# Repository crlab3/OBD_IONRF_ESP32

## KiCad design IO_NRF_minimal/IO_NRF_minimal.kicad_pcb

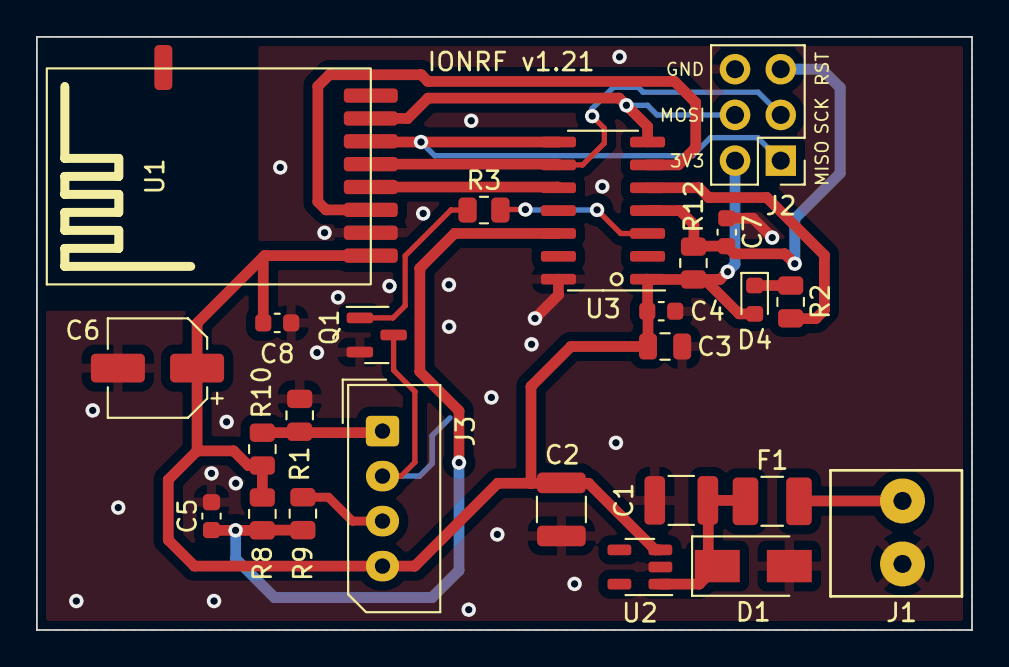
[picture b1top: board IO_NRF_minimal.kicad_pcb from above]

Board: 2 copper layers, 52.0 x 33.0 mm, 26 parts (1 on the bottom side), 18 nets.

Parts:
C1, C2: 10uF; C_1210_3225Metric
C3: 4.7uF; C_0805_2012Metric
C4, C5, C7, C8: 100nF; C_0603_1608Metric
C6: 100uF; CP_Elec_5x5.3
D1: DO-214AC; D_SMA
D4: LED; LED_0603_1608Metric
F1: 100mA Polyfuse; Fuse_1210_3225Metric_Pad1.42x2.65mm_HandSolder
J1: 12V_IN; SORKAPOCS-3.5mm-2
J2: Programmer_Pins_SPI; PinHeader_2x03_P2.54mm_Vertical
J3: XKC-Y2S-IN; Molex_SPOX_5267-04A_1x04_P2.50mm_Vertical
JP1: SolderJumper_2_Open; SolderJumper-2_P1.3mm_Open_RoundedPad1.0x1.5mm
Q1: BC847B; SOT-23
R1, R2, R3, R8, R9, R10, R12: 1k; R_0805_2012Metric
U1: NRF24L01_SMD
U2: AP7370-33WW-7; SOT-23-5
U3: ATtiny84-20SS; SOIC-14_3.9x8.7mm_P1.27mm

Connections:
/3V3: C2.1, C3.1, C4.1, C6.1, C8.2, D4.2 (A), J2.2, J3.4, R8.1, R10.1, R12.1, U1.1 (3V3), U2.3 (VOUT(3.3V)), U3.1 (VCC)
/ACC_12V_IN: F1.2, J1.2
/ACC_12V_PROT: C1.1, D1.1 (K), F1.1, U2.1 (VIN)
/MCU_MISO: J2.1, U1.6 (MOSI), U3.8 (PA5)
/MCU_MOSI: J2.4, U1.7 (MISO), U3.7 (PA6)
/MCU_RESET: C7.2, J2.5, R12.2, U3.4 (~RESET/PB3)
/MCU_SCK: J2.3, U1.5 (SCK), U3.9 (PA4)
/NRF_CE: U1.3 (CE), U3.6 (PA7)
/NRF_CS: U1.4 (CSN), U3.10 (PA3)
/XKC-Y2S-IN: C5.2, R8.2, R9.2, U3.12 (PA1)
/XKC_ACTIVATE: R3.2, U3.3 (XTAL2/PB1)
GND: C1.2, C2.2, C3.2, C4.2, C5.1, C6.2, C7.1, C8.1, D1.2 (A), J1.1, J2.6, JP1.1 (A), Q1.2 (E), R1.1, U1.2 (GND), U2.2 (GND), U3.14 (GND)
unnamed: D4.1 (K), R2.1
unnamed: J3.1, R1.2, R10.2
unnamed: J3.2, JP1.2 (B), Q1.3 (C)
unnamed: J3.3, R9.1
unnamed: Q1.1 (B), R3.1
unnamed: R2.2, U3.5 (PB2)

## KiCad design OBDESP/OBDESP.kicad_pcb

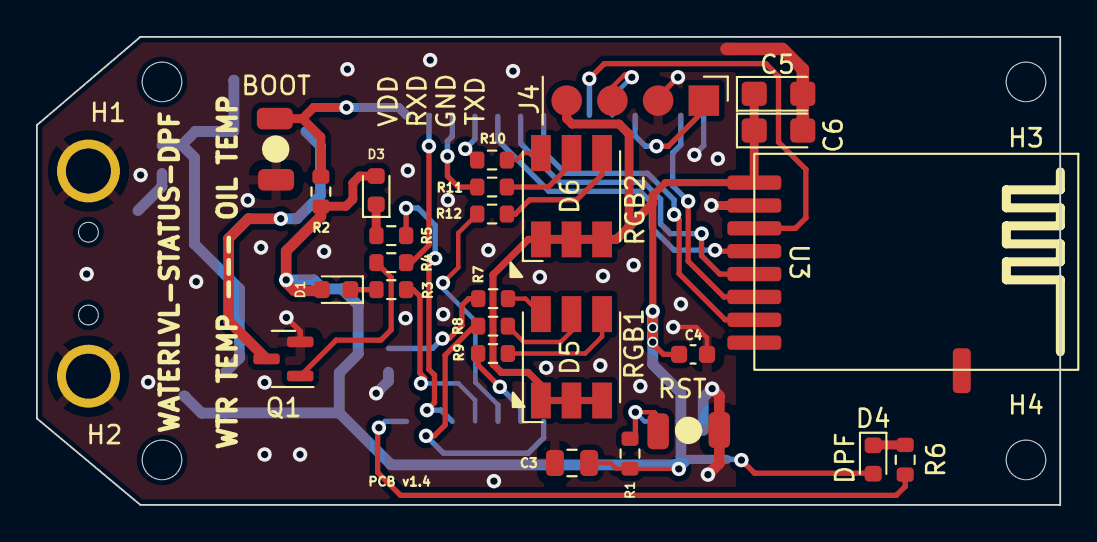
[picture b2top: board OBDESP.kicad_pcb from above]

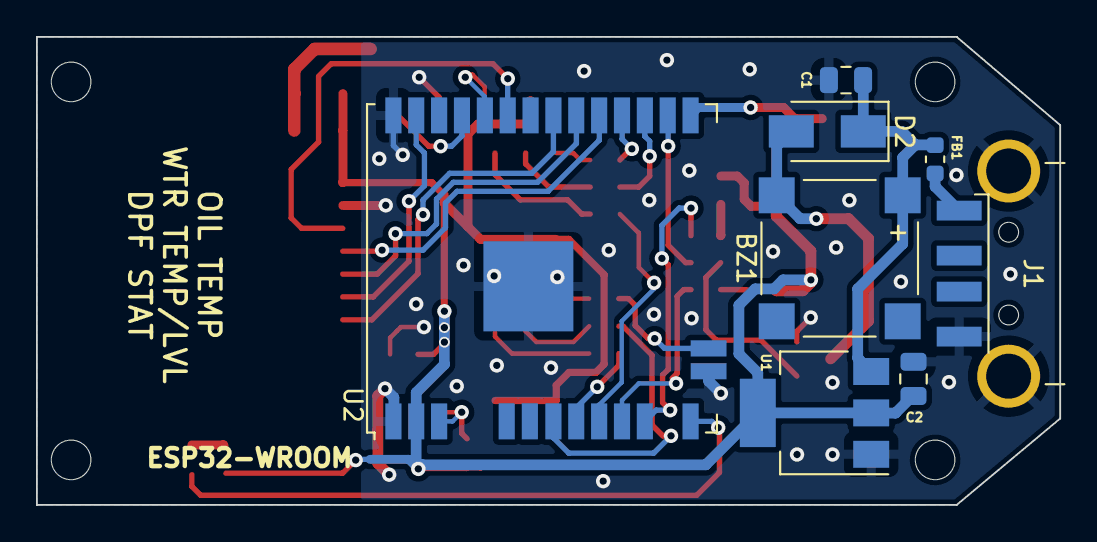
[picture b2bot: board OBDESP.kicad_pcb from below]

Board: 2 copper layers, 56.8 x 26.0 mm, 38 parts (8 on the bottom side), 34 nets.

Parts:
BZ1: Buzzer; PUIAudio_SMT_0825_S_4_R
C1, C2, C3: 10uF; C_0805_2012Metric
C4: 100nF; C_0603_1608Metric
C5, C6: 22uF; CP_EIA-3216-18_Kemet-A
D1: GREEN_LED; LED_0603_1608Metric
D2: D; D_SMA
D3: YELLOW_LED; LED_0603_1608Metric
D4: WHITE_LED; LED_0603_1608Metric
D5, D6: LED_RGB; LED_RGB_5050-6
FB1: FerriteBead_Small; L_0603_1608Metric
H1, H2, H3, H4: MountingHole; MountingHole_2.2mm_M2_DIN965
J1: USB_A; USB_A_CNCTech_1001-011-01101_Horizontal
J2: RST; B3U-1000P_Button
J3: BOOT; B3U-1000P_Button
J4: UART; PinHeader_1x04_P2.54mm_Vertical
Q1: BC848CLT1G; SOT-23
R1, R2: 10k; R_0603_1608Metric
R3, R4, R5: 220; R_0603_1608Metric
R6, R7, R8, R9, R10, R11, R12: 100; R_0603_1608Metric
U1: NCP1117-3.3_DPAK; SOT-223-3_TabPin2
U2: ESP32-WROOM-32; ESP32-WROOM-32U
U3: NRF24L01_SMD

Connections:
/3.3V: C2.2, C3.1, C4.1, C5.1, C6.1, D1.2 (A), D3.2 (A), D4.2 (A), D5.1 (RA), D5.2 (GA), D5.3 (BA), D6.1 (RA), D6.2 (GA), D6.3 (BA), J4.4, R1.1, R2.1, U1.2 (VO), U2.2 (VDD), U3.1 (3V3)
/COOLANTSTATUS_LED: R5.1, U2.12 (IO27)
/DPF_LED: R6.1, U2.14 (IO12)
/NRF_CE: U2.33 (IO21), U3.3 (CE)
/NRF_CSN: U2.29 (IO5), U3.4 (CSN)
/NRF_MISO: U2.31 (IO19), U3.7 (MISO)
/NRF_MOSI: U2.37 (IO23), U3.6 (MOSI)
/NRF_SCK: U2.30 (IO18), U3.5 (SCK)
/RGB1_B: R9.1, U2.9 (IO33)
/RGB1_G: R7.1, U2.16 (IO13)
/RGB1_R: R8.1, U2.8 (IO32)
/RGB2_B: R12.1, U2.10 (IO25)
/RGB2_G: R10.1, U2.28 (IO17)
/RGB2_R: R11.1, U2.27 (IO16)
/STATUS1_LED: R3.1, U2.11 (IO26)
/VIN: BZ1.1 (-), C1.2, D2.1 (K), FB1.2, U1.3 (VI)
/WARNING_BUZZER: R4.1, U2.26 (IO4)
GND: C1.1, C2.1, C3.2, C4.2, C5.2, C6.2, J1.4 (GND), J1.5 (Shield), J2.1, J3.1, J4.2, Q1.2 (E), U1.1 (GND), U2.1 (GND), U2.15 (GND), U2.38 (GND), U2.39 (GND), U3.2 (GND)
unnamed: BZ1.2 (+), D2.2 (A), Q1.3 (C)
unnamed: D1.1 (K), R3.2
unnamed: D5.4 (BK), R9.2
unnamed: D5.5 (GK), R8.2
unnamed: D5.6 (RK), R7.2
unnamed: D6.4 (BK), R12.2
unnamed: D6.5 (GK), R11.2
unnamed: D6.6 (RK), R10.2
unnamed: FB1.1, J1.1 (VBUS)
unnamed: J2.2, R1.2, U2.3 (EN)
unnamed: J3.2, R2.2, U2.25 (IO0)
unnamed: J4.1, U2.35 (TXD0/IO1)
unnamed: J4.3, U2.34 (RXD0/IO3)
unnamed: Q1.1 (B), R4.2
unnamed: D3.1 (K), R5.2
unnamed: D4.1 (K), R6.2

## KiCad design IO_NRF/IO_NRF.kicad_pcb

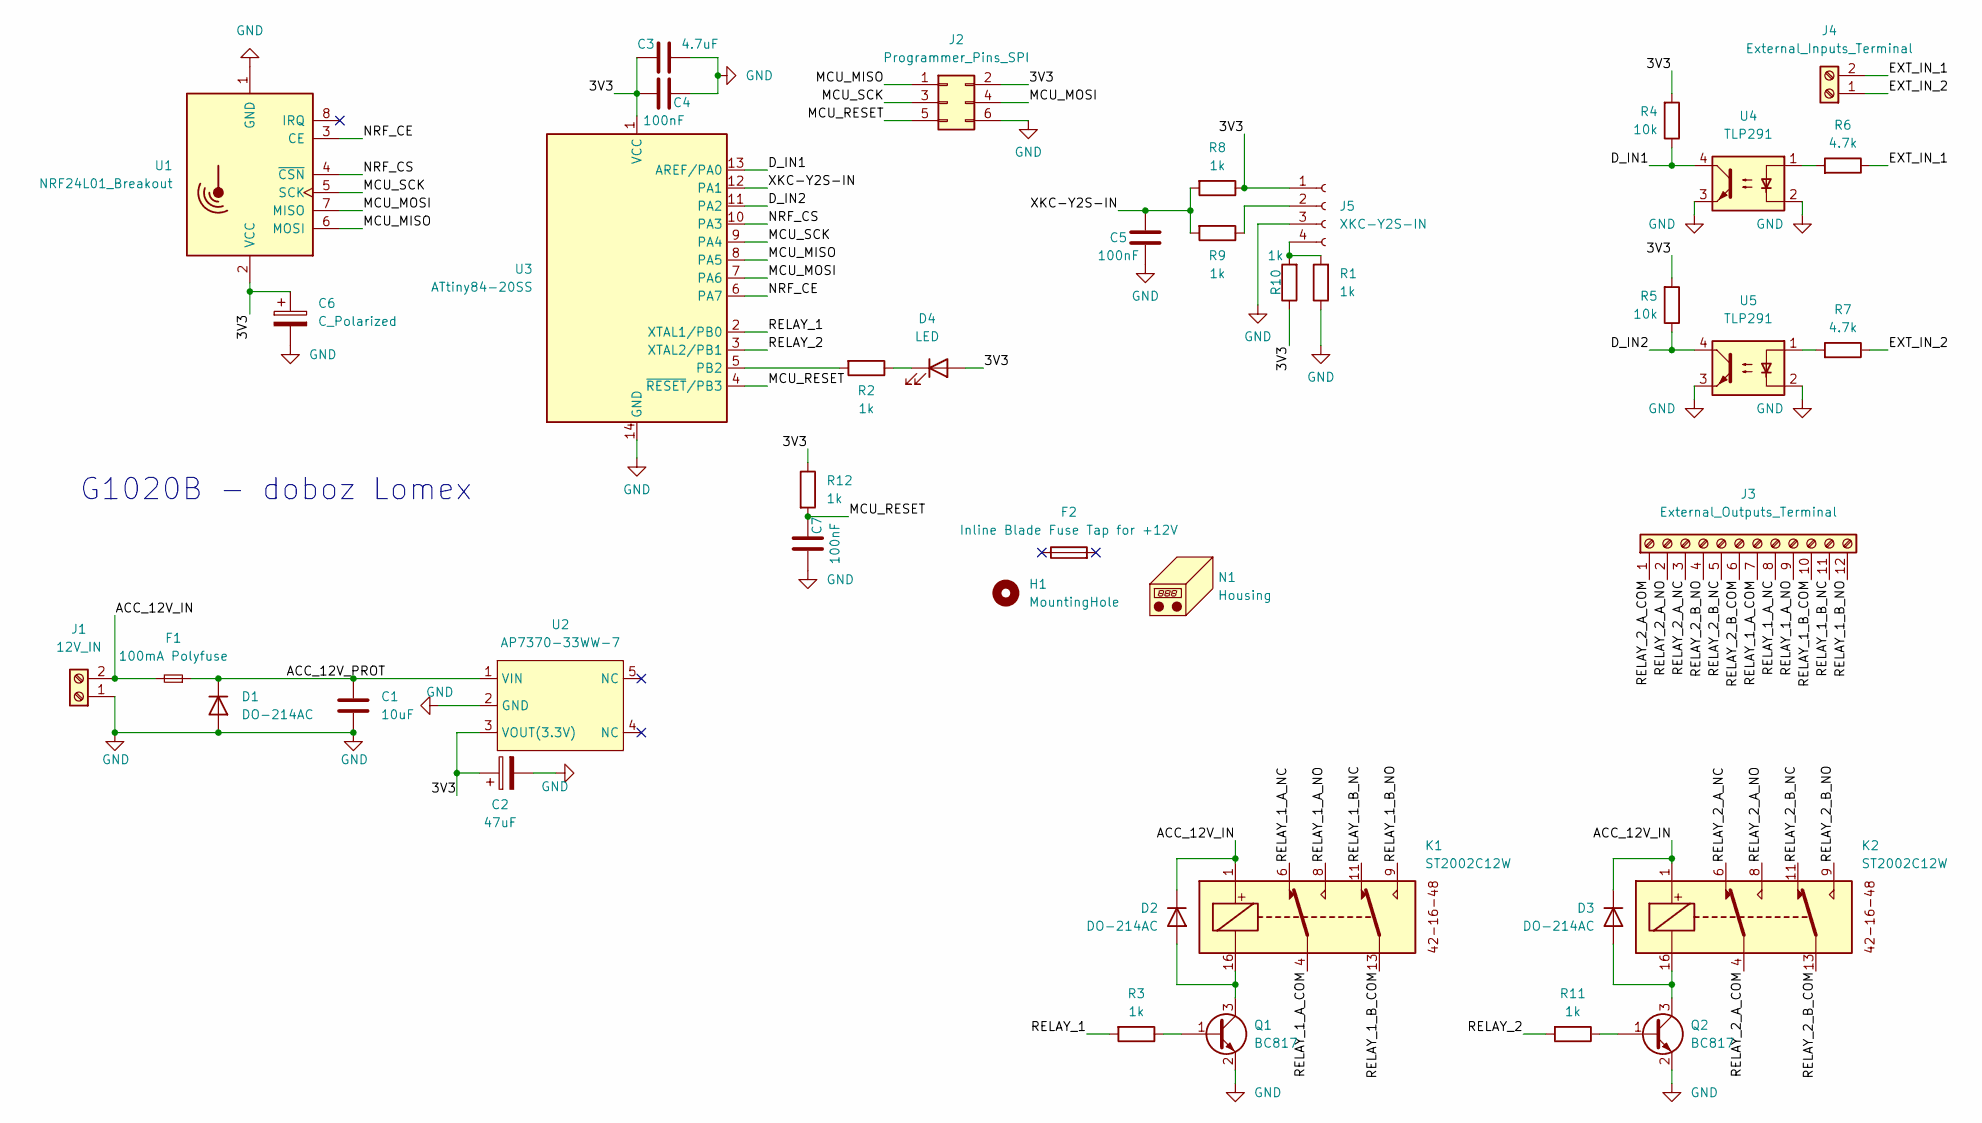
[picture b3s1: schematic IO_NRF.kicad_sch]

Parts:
C1: 10uF; C_1210_3225Metric
C2: 47uF; CP_Elec_6.3x5.4
C3: 4.7uF; C_0805_2012Metric
C4, C5, C7: 100nF; C_0603_1608Metric
C6: C_Polarized; CP_Elec_5x5.3
D1, D2, D3: DO-214AC; D_SMA
D4: LED; LED_0603_1608Metric
F1: 100mA Polyfuse; Fuse_1210_3225Metric_Pad1.42x2.65mm_HandSolder
F2: Inline Blade Fuse Tap for +12V; Farnell 3227155
H1: MountingHole; MountingHole_3.2mm_M3
J1: 12V_IN; SORKAPOCS-3.5mm-2
J2: Programmer_Pins_SPI; PinHeader_2x03_P2.54mm_Vertical
J3: External_Outputs_Terminal; SORKAPOCS-3.5mm-12
J4: External_Inputs_Terminal; SORKAPOCS-3.5mm-2
J5: XKC-Y2S-IN; PinSocket_1x04_P2.54mm_Vertical
K1, K2: ST2002C12W
N1: Housing
Q1, Q2: BC817; SOT-23
R1, R2, R3, R8, R9, R10, R11, R12: 1k; R_0805_2012Metric
R4, R5: 10k; R_0805_2012Metric
R6, R7: 4.7k; R_0805_2012Metric
U1: NRF24L01_Breakout; PinHeader_2x04_P2.54mm_Vertical
U2: AP7370-33WW-7; SOT-23-5; Mouser 621-AP7370-33WW-7
U3: ATtiny84-20SS; SOIC-14_3.9x8.7mm_P1.27mm; Mouser 556-ATTINY84-20SSUR
U4, U5: TLP291; SOIC-4_4.55x2.6mm_P1.27mm

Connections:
/3V3: C2.1, C3.1, C4.1, C6.1, D4.2 (A), J2.2, J5.1, R4.2, R5.2, R8.1, R10.1, R12.1, U1.2 (VCC), U2.3 (VOUT(3.3V)), U3.1 (VCC)
/ACC_12V_IN: D2.1 (K), D3.1 (K), F1.2, J1.2, K1.1, K2.1
/ACC_12V_PROT: C1.1, D1.1 (K), F1.1, U2.1 (VIN)
/D_IN1: R4.1, U3.13 (AREF/PA0), U4.4
/D_IN2: R5.1, U3.11 (PA2), U5.4
/EXT_IN_1: J4.2, R6.1
/EXT_IN_2: J4.1, R7.1
/MCU_MISO: J2.1, U1.6 (MOSI), U3.8 (PA5)
/MCU_MOSI: J2.4, U1.7 (MISO), U3.7 (PA6)
/MCU_RESET: C7.2, J2.5, R12.2, U3.4 (~RESET/PB3)
/MCU_SCK: J2.3, U1.5 (SCK), U3.9 (PA4)
/NRF_CE: U1.3 (CE), U3.6 (PA7)
/NRF_CS: U1.4 (~CSN), U3.10 (PA3)
/RELAY_1: R3.2, U3.2 (XTAL1/PB0)
/RELAY_1_A_COM: J3.7, K1.4
/RELAY_1_A_NC: J3.8, K1.6
/RELAY_1_A_NO: J3.9, K1.8
/RELAY_1_B_COM: J3.10, K1.13
/RELAY_1_B_NC: J3.11, K1.11
/RELAY_1_B_NO: J3.12, K1.9
/RELAY_2: R11.2, U3.3 (XTAL2/PB1)
/RELAY_2_A_COM: J3.1, K2.4
/RELAY_2_A_NC: J3.3, K2.6
/RELAY_2_A_NO: J3.2, K2.8
/RELAY_2_B_COM: J3.6, K2.13
/RELAY_2_B_NC: J3.5, K2.11
/RELAY_2_B_NO: J3.4, K2.9
/XKC-Y2S-IN: C5.2, R8.2, R9.2, U3.12 (PA1)
GND: C1.2, C2.2, C3.2, C4.2, C5.1, C6.2, C7.1, D1.2 (A), J1.1, J2.6, J5.3, Q1.2 (E), Q2.2 (E), R1.1, U1.1 (GND), U2.2 (GND), U3.14 (GND), U4.2, U4.3, U5.2, U5.3
unnamed: D2.2 (A), K1.16, Q1.3 (C)
unnamed: D3.2 (A), K2.16, Q2.3 (C)
unnamed: D4.1 (K), R2.1
unnamed: J5.2, R9.1
unnamed: J5.4, R1.2, R10.2
unnamed: Q1.1 (B), R3.1
unnamed: Q2.1 (B), R11.1
unnamed: R2.2, U3.5 (PB2)
unnamed: R6.2, U4.1
unnamed: R7.2, U5.1

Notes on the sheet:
G1020B - doboz Lomex

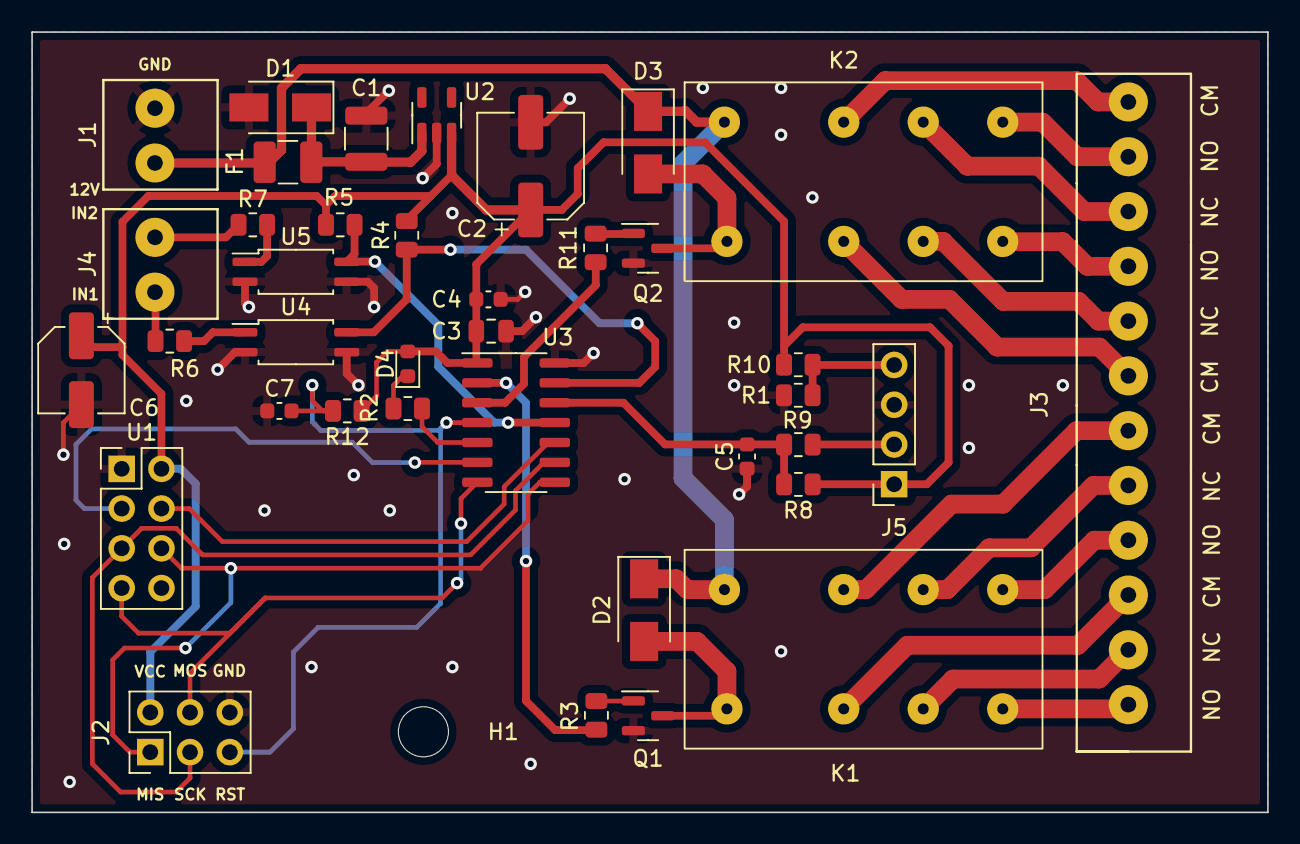
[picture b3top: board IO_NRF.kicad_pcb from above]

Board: 2 copper layers, 79.0 x 49.9 mm, 39 parts (0 on the bottom side), 39 nets.

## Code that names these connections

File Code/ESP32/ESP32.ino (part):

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#define RES_PWM 10
#define LED_MAX 1023

#define NRF_CE 21
#define NRF_CS 5

#define OBD_UPDATE_INTERVAL 100
#define COOLANT_LOW_LIMIT 10
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#define RGB_RIGHT_GREEN 17
#define RGB_RIGHT_BLUE 25 

#define DPF_LED 12
#define STATUS1_LED 26
#define CLNTSTATUS_LED 27

#define BUZZER_PIN 4
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
  //-------------------SETUP LEDs---------------------
  
  uint8_t LEDPins[9]={RGB_RIGHT_RED,RGB_RIGHT_GREEN,RGB_RIGHT_BLUE,RGB_LEFT_RED,RGB_LEFT_GREEN,RGB_LEFT_BLUE,DPF_LED,STATUS1_LED,CLNTSTATUS_LED};
  int i = 0;
  for(i=0; i<9; i++)
  {
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
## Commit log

2022-12-18 Initial commit 1
    New commit for repo
2022-12-31 NRF24L01 Communicating on ESP32 & ATTINY84
    IONRF + ESP32 for NRF24L01 TESTED OK.
    PCBs are fixed.
2023-01-01 Fixed RGD Red TONE at ESP32, IONRF sending live data OK
2023-01-02 IONRF: millis() implemented
2023-01-02 ESP32 - New millis() timer, coolant level sense OK, test SW 1.0
    Everything works fine in car! Testing start now!
2023-01-06 fixed heatmap, left-right LED, now testing millis() cycle
2023-01-06 Timing working OK, ELM errors tested OK, Release 1.0
2023-01-06 Added Compiled Binary and Flash Tool Release v1.0-alpha
2023-01-06 Started manufacturing data collection
2023-01-07 Updated ODBESP32 PCB with LED separation larger.
2023-01-07 deleted PCB 3D OBDESP32 file
2023-01-08 Updated manufacturing xls
2023-01-13 Updated both PCBs with TEMT6000 and XKC enabler
2023-01-13 ESP32-added ADC functions untested! PCB update
    added capacitor for PCB design for ADC reading the TEMT6000 sensor
2023-01-13 IONRF code remade, to watchdog, untested!
2023-01-14 Minimalized IO-NRF, no Digital Input
2023-01-14 Updated BOMs, manufacturing (beültetés árak) and PCBs
2023-01-15 Uploaded codes to IONRF (Watchdog) & ESP32 now testing
2023-01-21 added bom-on kivuli list
2023-01-21 minimal xls update
    f
2023-01-24 Updated ESP32 software to support new OBDII types as well as previous types
2023-07-27 latest versions
2023-07-27 Light sensor parts eliminated from code. DEBUG_PORT - Off.
2023-07-27 This version turns on all debugging messages.
2024-03-10 updated constants and water level to 110C
